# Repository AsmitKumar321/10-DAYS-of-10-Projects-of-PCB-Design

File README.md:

# 10-DAYS-of-10-Projects-of-PCB-Design
DAY 01: AC to DC converter

DAY 02: Transformerless Power Supply

DAY 03: SERVO MOTOR TESTER

DAY 04: DC MOTOR SPEED CONTROLLER

DAY 05: USB TO UART CONVERTER

DAY 06: DC-DC BOOST CONVERTER

DAY 07: MOTOR DRIVER

DAY 08: 30A HOME AUTOMATION WITH ESP32 MCUP

DAY 09: 300 WATT SINE WAVE INVERTER

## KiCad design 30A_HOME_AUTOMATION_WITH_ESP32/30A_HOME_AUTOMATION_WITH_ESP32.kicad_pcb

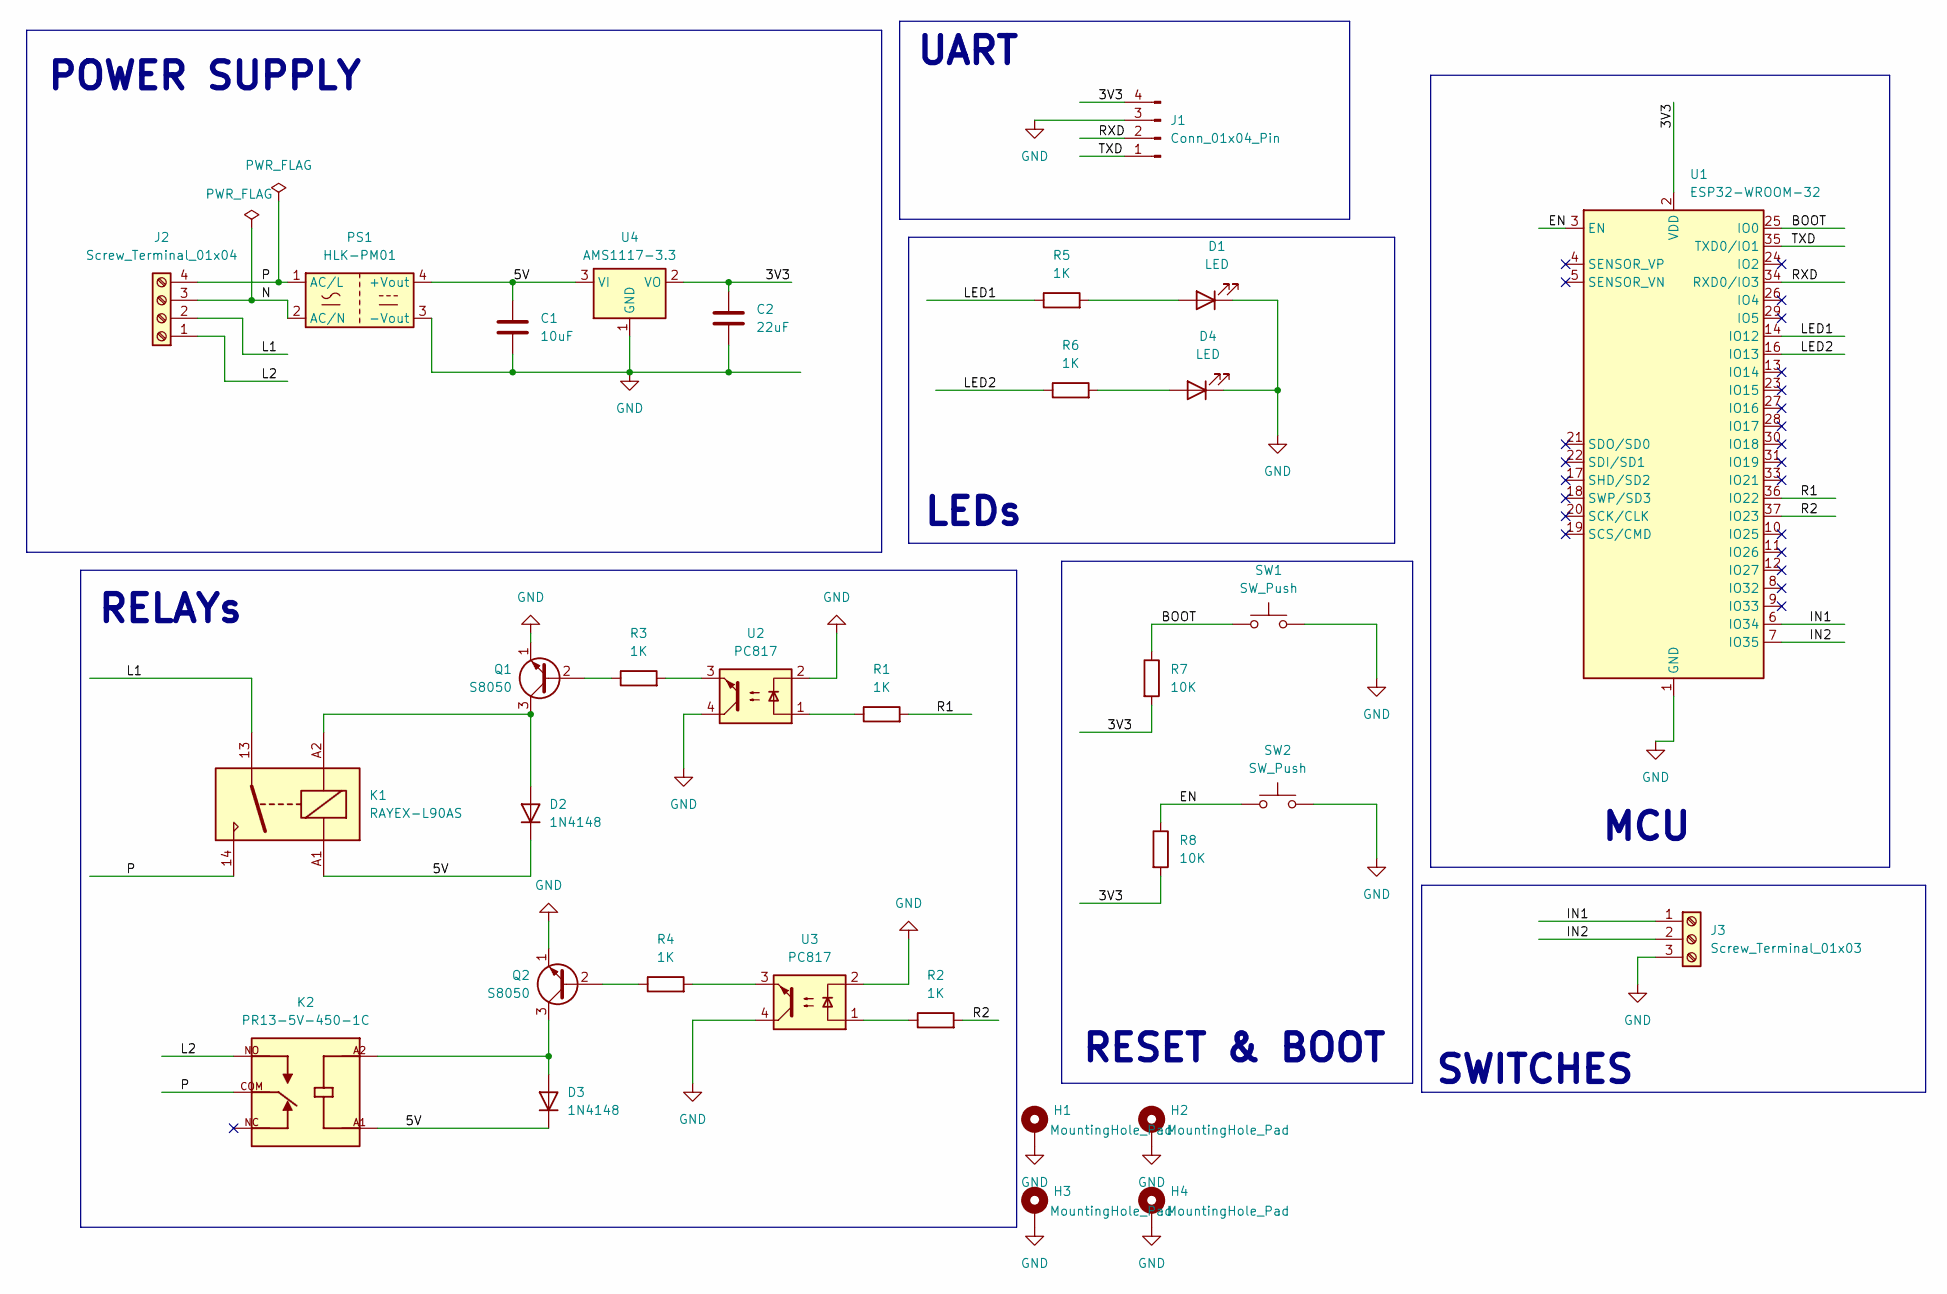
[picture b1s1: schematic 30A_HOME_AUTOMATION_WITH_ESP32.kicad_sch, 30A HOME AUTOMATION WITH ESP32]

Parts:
C1: 10uF; C_0805_2012Metric
C2: 22uF; C_0805_2012Metric
D1, D4: LED; LED_0805_2012Metric
D2, D3: 1N4148; D_DO-35_SOD27_P7.62mm_Horizontal
H1, H2, H3, H4: MountingHole_Pad; MountingHole_2.7mm_M2.5_Pad_Via
J1: Conn_01x04_Pin; PinHeader_1x04_P2.54mm_Vertical
J2: Screw_Terminal_01x04; TerminalBlock_bornier-4_P5.08mm
J3: Screw_Terminal_01x03; TerminalBlock_bornier-3_P5.08mm
K1: RAYEX-L90AS; Relay_SPST_RAYEX-L90AS
K2: PR13-5V-450-1C; RELAY_PR13-5V-450-1C; PARTREV 1.0
PS1: HLK-PM01; Converter_ACDC_Hi-Link_HLK-PMxx
Q1, Q2: S8050; TO-92_Inline
R1, R2, R3, R4, R5, R6: 1K; R_0805_2012Metric
R7, R8: 10K; R_0805_2012Metric
SW1, SW2: SW_Push; SW_PUSH_6mm
U1: ESP32-WROOM-32
U2, U3: PC817; DIP-4_W7.62mm
U4: AMS1117-3.3; SOT-223-3_TabPin2

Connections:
/3V3: C2.1, J1.4, R7.2, R8.2, U1.2 (VDD), U4.2 (VO)
/5V: C1.1, D2.1 (K), D3.1 (K), K1.A1, K2.A1, PS1.4 (+Vout), U4.3 (VI)
/BOOT: R7.1, SW1.1, U1.25 (IO0)
/EN: R8.1, SW2.1, U1.3 (EN)
/IN1: J3.1, U1.6 (IO34)
/IN2: J3.2, U1.7 (IO35)
/L1: J2.2, K1.13
/L2: J2.1, K2.NO
/LED1: R5.1, U1.14 (IO12)
/LED2: R6.1, U1.16 (IO13)
/N: J2.3, PS1.2 (AC/N)
/P: J2.4, K1.14, K2.COM, PS1.1 (AC/L)
/R1: R1.2, U1.36 (IO22)
/R2: R2.2, U1.37 (IO23)
/RXD: J1.2, U1.34 (RXD0/IO3)
/TXD: J1.1, U1.35 (TXD0/IO1)
GND: C1.2, C2.2, D1.1 (K), D4.1 (K), H1.1, H2.1, H3.1, H4.1, J1.3, J3.3, PS1.3 (-Vout), Q1.1 (E), Q2.1 (E), SW1.2, SW2.2, U1.1 (GND), U1.15 (GND), U1.38 (GND), U1.39 (GND), U2.2, U2.4, U3.2, U3.4, U4.1 (GND)
unnamed: D1.2 (A), R5.2
unnamed: D2.2 (A), K1.A2, Q1.3 (C)
unnamed: D3.2 (A), K2.A2, Q2.3 (C)
unnamed: D4.2 (A), R6.2
unnamed: Q1.2 (B), R3.1
unnamed: Q2.2 (B), R4.1
unnamed: R1.1, U2.1
unnamed: R2.1, U3.1
unnamed: R3.2, U2.3
unnamed: R4.2, U3.3

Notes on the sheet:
SWITCHES
LEDs
RELAYs
UART
RESET & BOOT
POWER SUPPLY
MCU

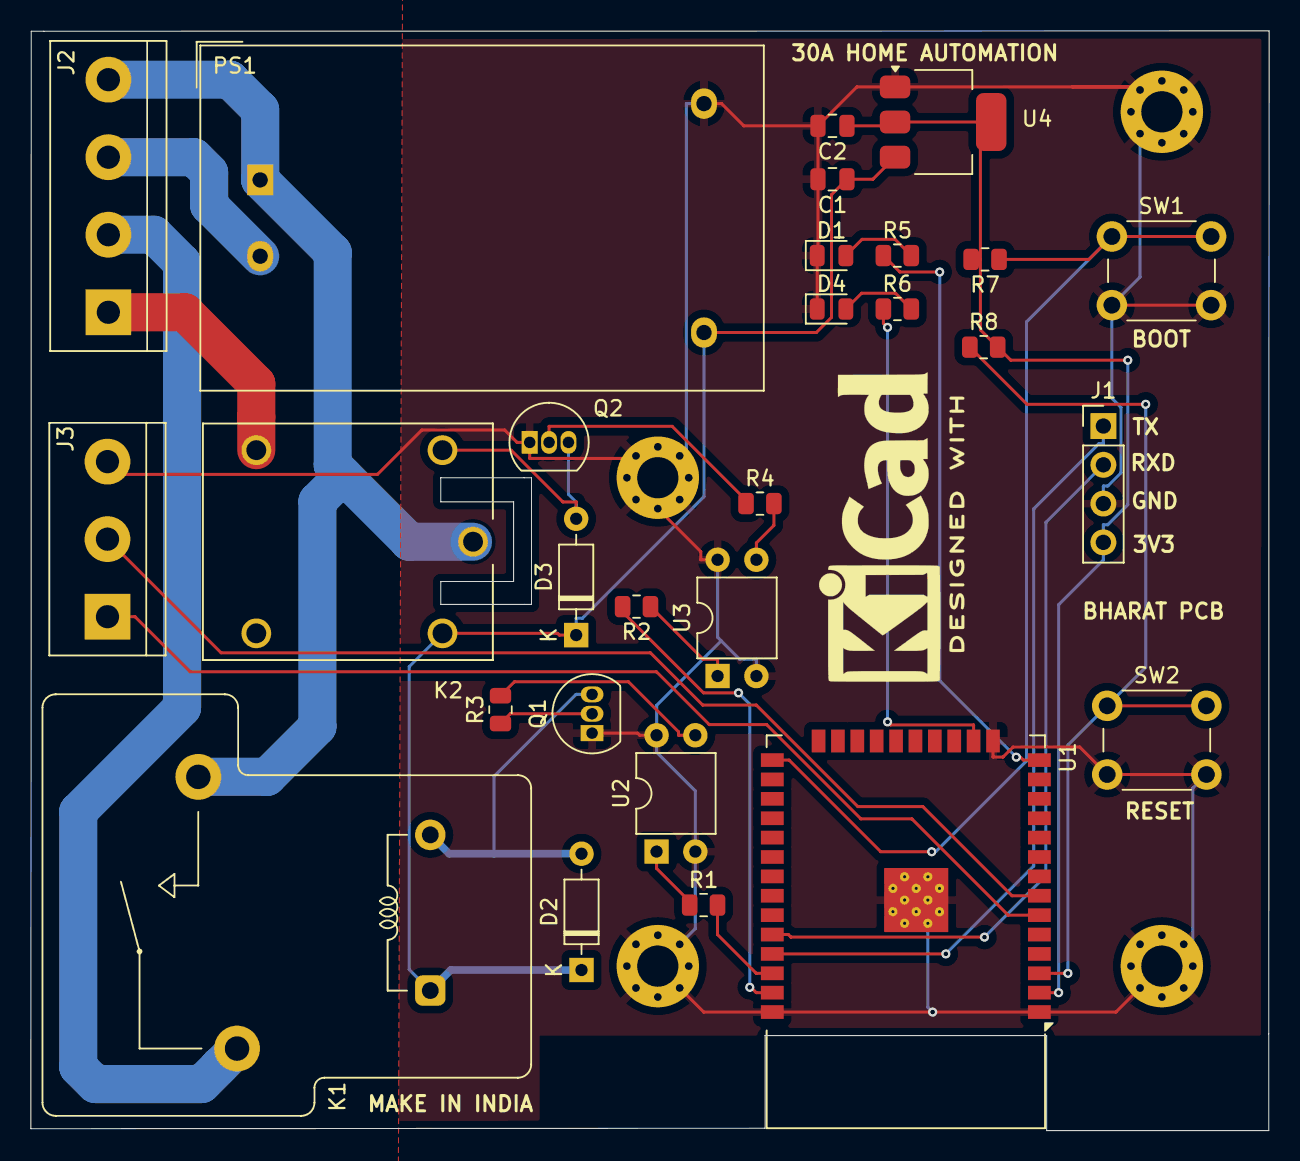
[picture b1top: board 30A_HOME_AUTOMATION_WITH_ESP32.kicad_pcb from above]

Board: 2 copper layers, 81.1 x 72.1 mm, 32 parts (0 on the bottom side), 27 nets.

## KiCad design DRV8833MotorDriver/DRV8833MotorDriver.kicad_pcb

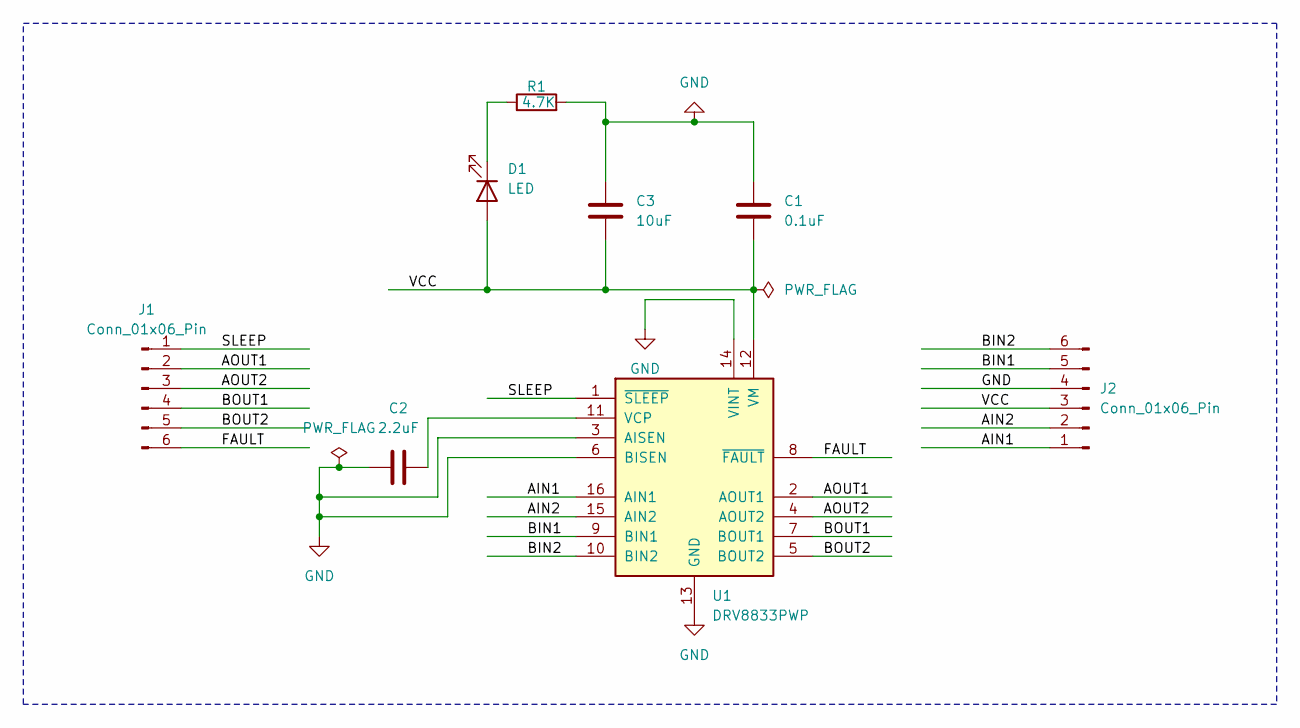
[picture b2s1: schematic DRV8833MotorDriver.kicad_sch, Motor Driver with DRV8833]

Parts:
C1: 0.1uF; C_0805_2012Metric
C2: 2.2uF; C_0805_2012Metric
C3: 10uF; CP_EIA-6032-20_AVX-F
D1: LED; LED_0805_2012Metric
J1, J2: Conn_01x06_Pin; PinHeader_1x06_P2.54mm_Vertical
R1: 4.7K; R_0805_2012Metric
U1: DRV8833PWP; HTSSOP-16-1EP_4.4x5mm_P0.65mm_EP3.4x5mm_Mask2.46x2.31mm_The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

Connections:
/AIN1: J2.1, U1.16 (AIN1)
/AIN2: J2.2, U1.15 (AIN2)
/AOUT1: J1.2, U1.2 (AOUT1)
/AOUT2: J1.3, U1.4 (AOUT2)
/BIN1: J2.5, U1.9 (BIN1)
/BIN2: J2.6, U1.10 (BIN2)
/BOUT1: J1.4, U1.7 (BOUT1)
/BOUT2: J1.5, U1.5 (BOUT2)
/FAULT: J1.6, U1.8 (~FAULT)
/SLEEP: J1.1, U1.1 (~SLEEP)
/VCC: C1.2, C3.2, D1.2 (A), J2.3, U1.12 (VM)
GND: C1.1, C2.1, C3.1, J2.4, R1.2, U1.3 (AISEN), U1.6 (BISEN), U1.13 (GND), U1.14 (VINT), U1.17 (GND)
unnamed: D1.1 (K), R1.1
unnamed: C2.2, U1.11 (VCP)

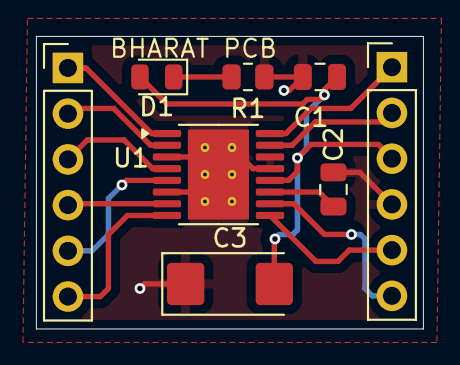
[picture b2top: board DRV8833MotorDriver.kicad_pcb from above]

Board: 2 copper layers, 21.5 x 16.2 mm, 8 parts (0 on the bottom side), 14 nets.

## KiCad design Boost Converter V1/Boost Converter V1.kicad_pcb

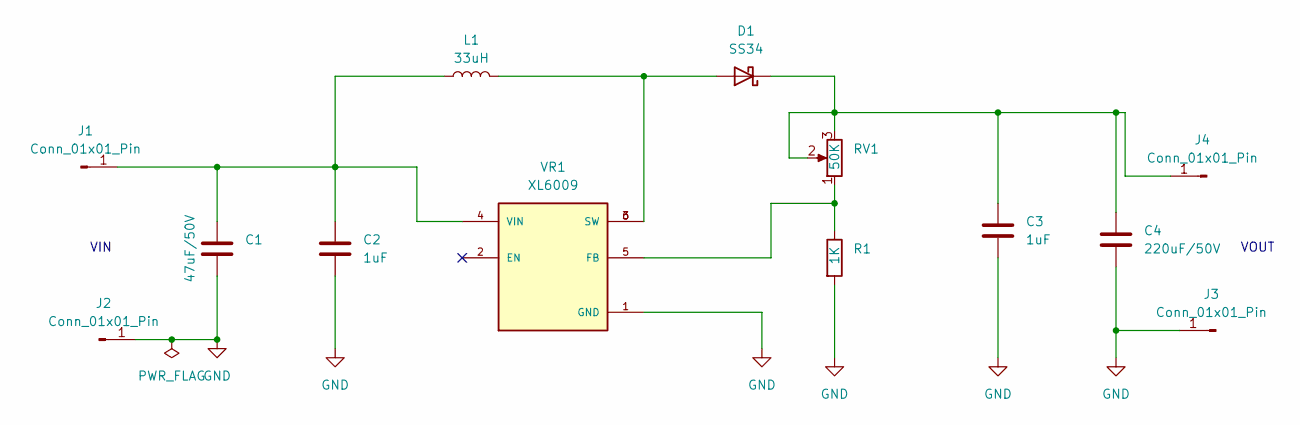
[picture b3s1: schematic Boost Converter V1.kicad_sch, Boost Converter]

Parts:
C1: 47uF/50V; C_Radial_D6.3mm_H11.0mm_P2.50mm
C2, C3: 1uF; C_0805_2012Metric
C4: 220uF/50V; C_Radial_D6.3mm_H11.0mm_P2.50mm
D1: SS34; D_SMA
J1, J2, J3, J4: Conn_01x01_Pin; PinHeader_1x01_P2.54mm_Vertical
L1: 33uH; L_12x12mm_H8mm
R1: 1K; R_1206_3216Metric
RV1: 50K; Potentiometer_Bourns_3296W_Vertical
VR1: XL6009; DPAK170P1435X465-6N; PARTREV 1.1

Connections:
GND: C1.2, C2.2, C3.2, C4.2, J2.1, J3.1, R1.2, VR1.1 (GND)
unnamed: D1.2 (A), L1.2, VR1.3 (SW), VR1.6 (SW)
unnamed: C3.1, C4.1, D1.1 (K), J4.1, RV1.2, RV1.3
unnamed: C1.1, C2.1, J1.1, L1.1, VR1.4 (VIN)
unnamed: R1.1, RV1.1, VR1.5 (FB)

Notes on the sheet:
VIN
VOUT

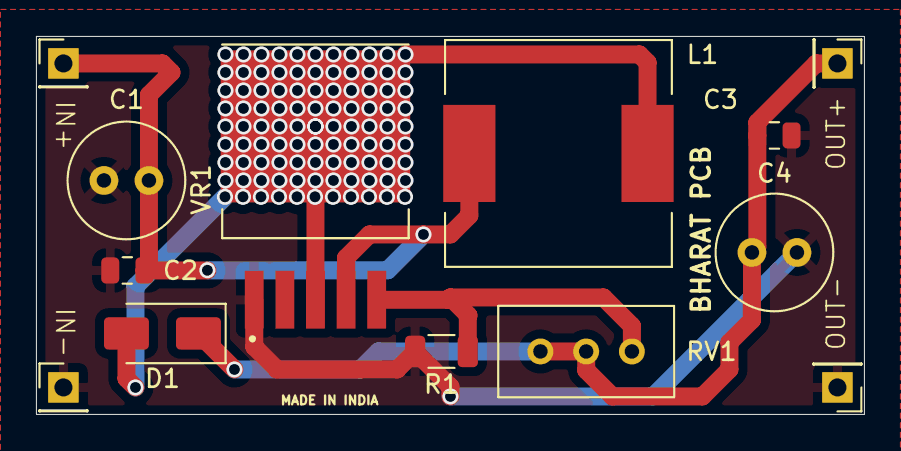
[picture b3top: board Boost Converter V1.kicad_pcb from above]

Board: 2 copper layers, 46.0 x 21.0 mm, 13 parts (0 on the bottom side), 5 nets.

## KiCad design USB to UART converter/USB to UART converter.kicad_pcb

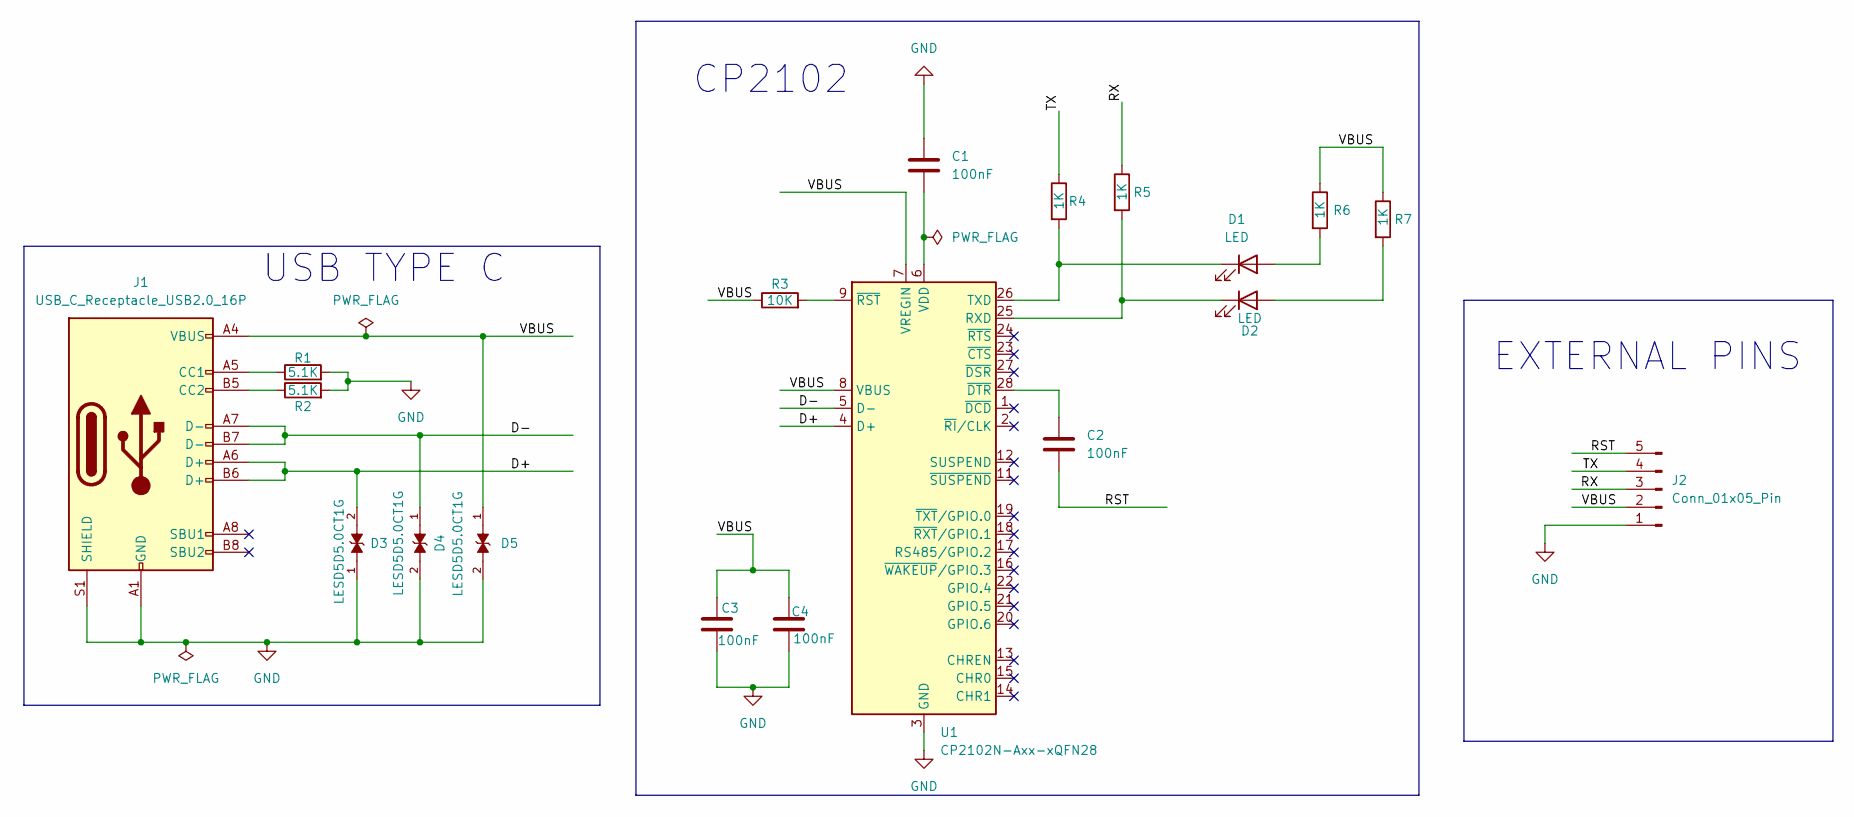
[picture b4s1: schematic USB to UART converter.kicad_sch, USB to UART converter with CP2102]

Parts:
C1, C2, C3, C4: 100nF; C_0201_0603Metric
D1, D2: LED; LED_0201_0603Metric
D3, D4, D5: LESD5D5.0CT1G; TVS_LESD5D5.0CT1G; PARTREV O
J1: USB_C_Receptacle_USB2.0_16P; USB_C_Receptacle_HRO_TYPE-C-31-M-12
J2: Conn_01x05_Pin; PinHeader_1x05_P2.54mm_Horizontal
R1, R2: 5.1K; R_0201_0603Metric
R3: 10K; R_0201_0603Metric
R4, R5, R6, R7: 1K; R_0201_0603Metric
U1: CP2102N-Axx-xQFN28; QFN-28-1EP_5x5mm_P0.5mm_EP3.35x3.35mm

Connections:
/D+: D3.2, J1.A6 (D+), J1.B6 (D+), U1.4 (D+)
/D-: D4.1, J1.A7 (D-), J1.B7 (D-), U1.5 (D-)
/RST: C2.2, J2.5
/RX: J2.3, R5.1
/TX: J2.4, R4.1
/VBUS: C3.1, C4.1, D5.1, J1.A4 (VBUS), J1.A9 (VBUS), J1.B4 (VBUS), J1.B9 (VBUS), J2.2, R3.1, R6.1, R7.1, U1.7 (VREGIN), U1.8 (VBUS)
GND: C1.1, C3.2, C4.2, D3.1, D4.2, D5.2, J1.A1 (GND), J1.A12 (GND), J1.B1 (GND), J1.B12 (GND), J1.S1 (SHIELD), J2.1, R1.2, R2.2, U1.3 (GND), U1.29 (GND)
unnamed: D1.2 (A), R6.2
unnamed: D1.1 (K), R4.2, U1.26 (TXD)
unnamed: D2.2 (A), R7.2
unnamed: D2.1 (K), R5.2, U1.25 (RXD)
unnamed: J1.A5 (CC1), R1.1
unnamed: J1.B5 (CC2), R2.1
unnamed: C1.2, U1.6 (VDD)
unnamed: C2.1, U1.28 (~DTR)
unnamed: R3.2, U1.9 (~RST)

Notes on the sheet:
CP2102
USB TYPE C
EXTERNAL PINS

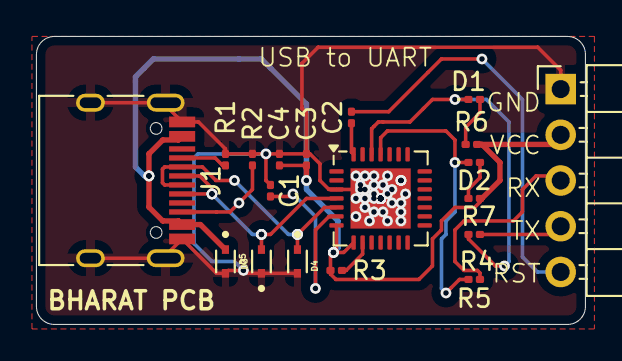
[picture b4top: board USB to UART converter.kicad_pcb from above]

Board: 2 copper layers, 30.5 x 16.0 mm, 19 parts (0 on the bottom side), 16 nets.

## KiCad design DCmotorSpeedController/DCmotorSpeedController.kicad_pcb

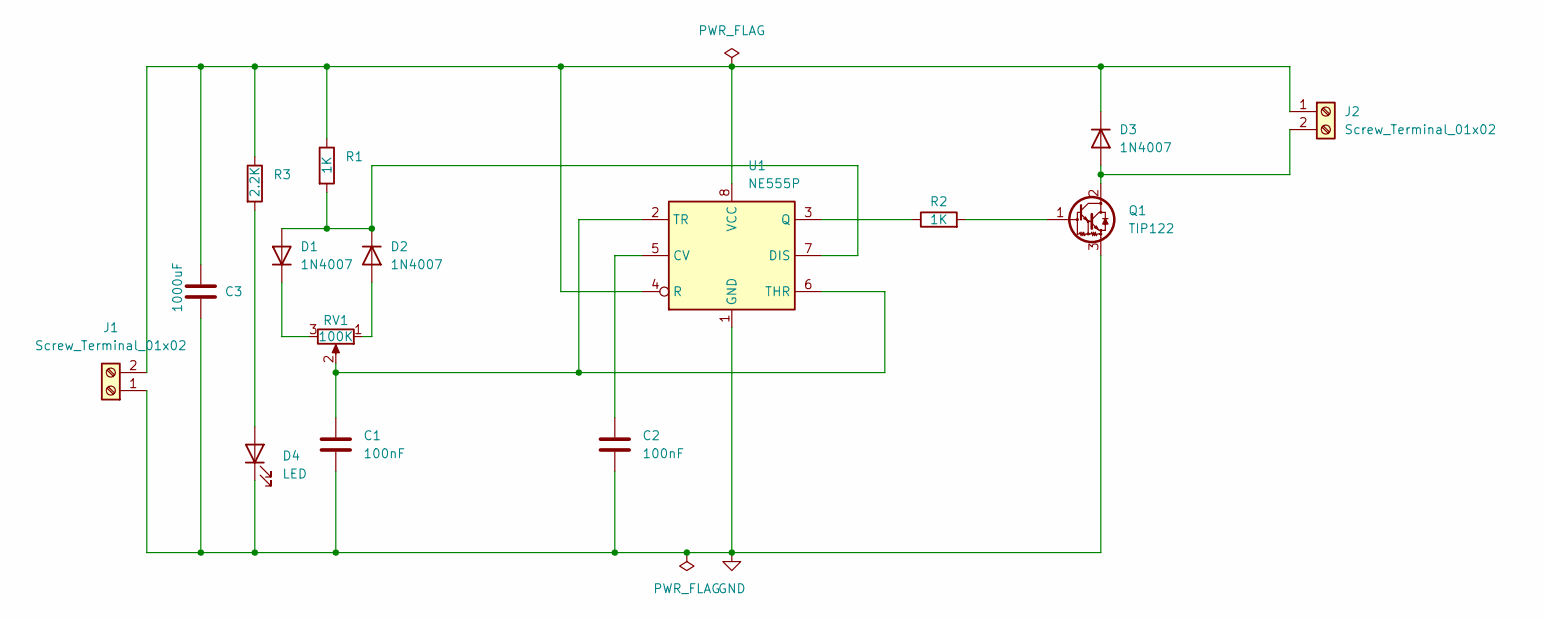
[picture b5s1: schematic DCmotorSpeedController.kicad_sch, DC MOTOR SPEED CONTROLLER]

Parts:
C1, C2: 100nF; C_Disc_D4.7mm_W2.5mm_P5.00mm
C3: 1000uF; CP_Radial_D10.0mm_P5.00mm
D1, D2, D3: 1N4007; D_DO-41_SOD81_P10.16mm_Horizontal
D4: LED; LED_D5.0mm
J1, J2: Screw_Terminal_01x02; TerminalBlock_bornier-2_P5.08mm
Q1: TIP122; TO-220-3_Vertical
R1, R2: 1K; R_Axial_DIN0204_L3.6mm_D1.6mm_P7.62mm_Horizontal
R3: 2.2K; R_Axial_DIN0204_L3.6mm_D1.6mm_P7.62mm_Horizontal
RV1: 100K; Potentiometer_Alps_RK163_Single_Horizontal
U1: NE555P; DIP-8_W7.62mm

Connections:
GND: C1.2, C2.2, C3.2, D4.1 (K), J1.1, Q1.3 (E), U1.1 (GND)
unnamed: D1.2 (A), D2.1 (K), R1.2, U1.7 (DIS)
unnamed: D1.1 (K), RV1.3
unnamed: D2.2 (A), RV1.1
unnamed: D3.2 (A), J2.2, Q1.2 (C)
unnamed: C3.1, D3.1 (K), J1.2, J2.1, R1.1, R3.1, U1.4 (R), U1.8 (VCC)
unnamed: D4.2 (A), R3.2
unnamed: Q1.1 (B), R2.2
unnamed: C2.1, U1.5 (CV)
unnamed: R2.1, U1.3 (Q)
unnamed: C1.1, RV1.2, U1.2 (TR), U1.6 (THR)

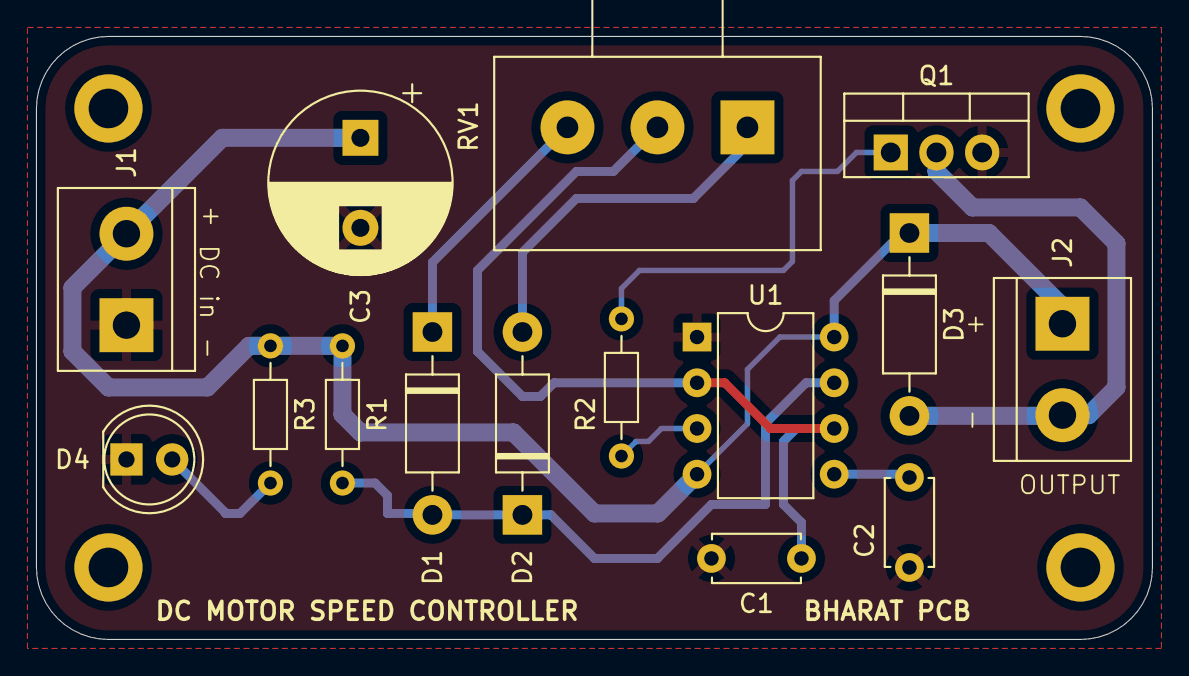
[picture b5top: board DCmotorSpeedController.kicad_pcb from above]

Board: 2 copper layers, 62.0 x 33.5 mm, 15 parts (0 on the bottom side), 11 nets.

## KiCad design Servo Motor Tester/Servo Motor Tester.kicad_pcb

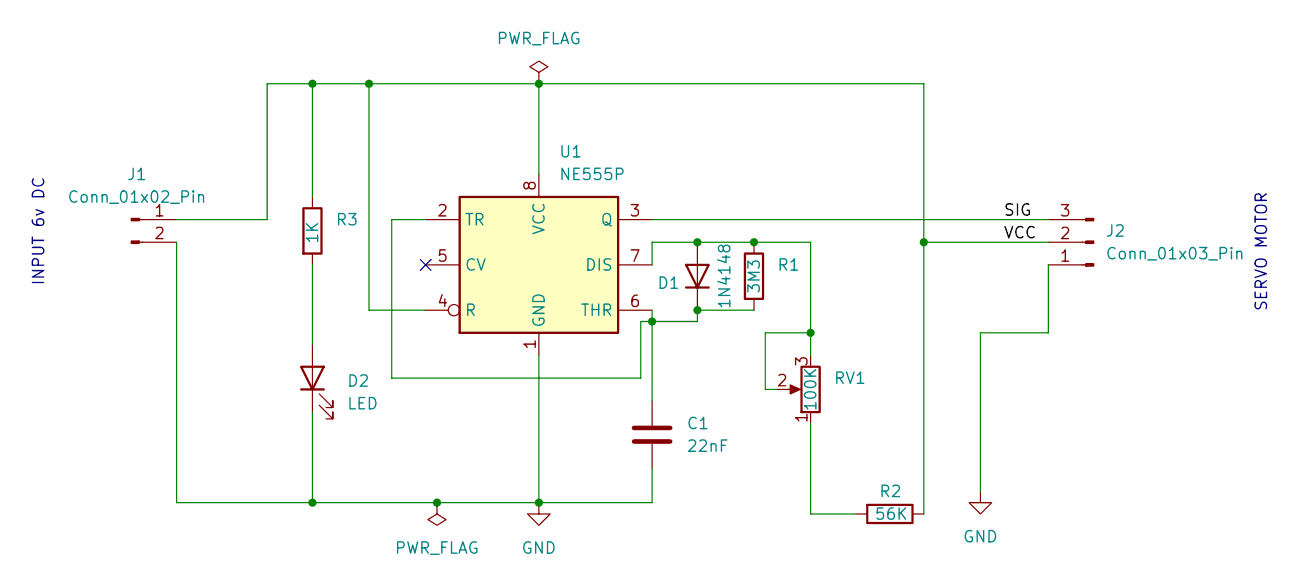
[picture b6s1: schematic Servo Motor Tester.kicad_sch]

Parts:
C1: 22nF; C_Disc_D4.3mm_W1.9mm_P5.00mm
D1: 1N4148; D_DO-35_SOD27_P7.62mm_Horizontal
D2: LED; LED_D3.0mm
J1: Conn_01x02_Pin; PinHeader_1x02_P2.54mm_Horizontal
J2: Conn_01x03_Pin; PinHeader_1x03_P2.54mm_Horizontal
R1: 3M3; R_Axial_DIN0204_L3.6mm_D1.6mm_P7.62mm_Horizontal
R2: 56K; R_Axial_DIN0204_L3.6mm_D1.6mm_P7.62mm_Horizontal
R3: 1K; R_Axial_DIN0204_L3.6mm_D1.6mm_P7.62mm_Horizontal
RV1: 100K; Potentiometer_Alps_RK163_Single_Horizontal
U1: NE555P; DIP-8_W7.62mm

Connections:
/SIG: J2.3, U1.3 (Q)
/VCC: J1.1, J2.2, R2.1, R3.1, U1.4 (R), U1.8 (VCC)
GND: C1.2, D2.1 (K), J1.2, J2.1, U1.1 (GND)
unnamed: D1.2 (A), R1.1, RV1.2, RV1.3, U1.7 (DIS)
unnamed: C1.1, D1.1 (K), R1.2, U1.2 (TR), U1.6 (THR)
unnamed: D2.2 (A), R3.2
unnamed: R2.2, RV1.1

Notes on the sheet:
INPUT 6v DC
SERVO MOTOR

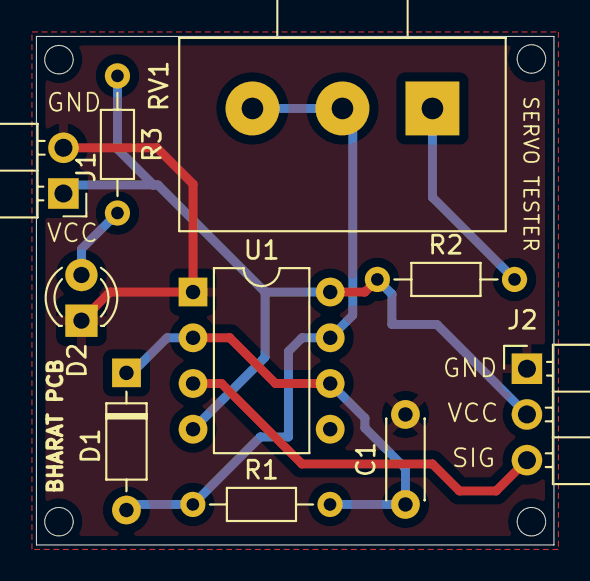
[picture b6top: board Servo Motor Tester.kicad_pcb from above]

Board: 2 copper layers, 28.8 x 28.2 mm, 10 parts (0 on the bottom side), 7 nets.

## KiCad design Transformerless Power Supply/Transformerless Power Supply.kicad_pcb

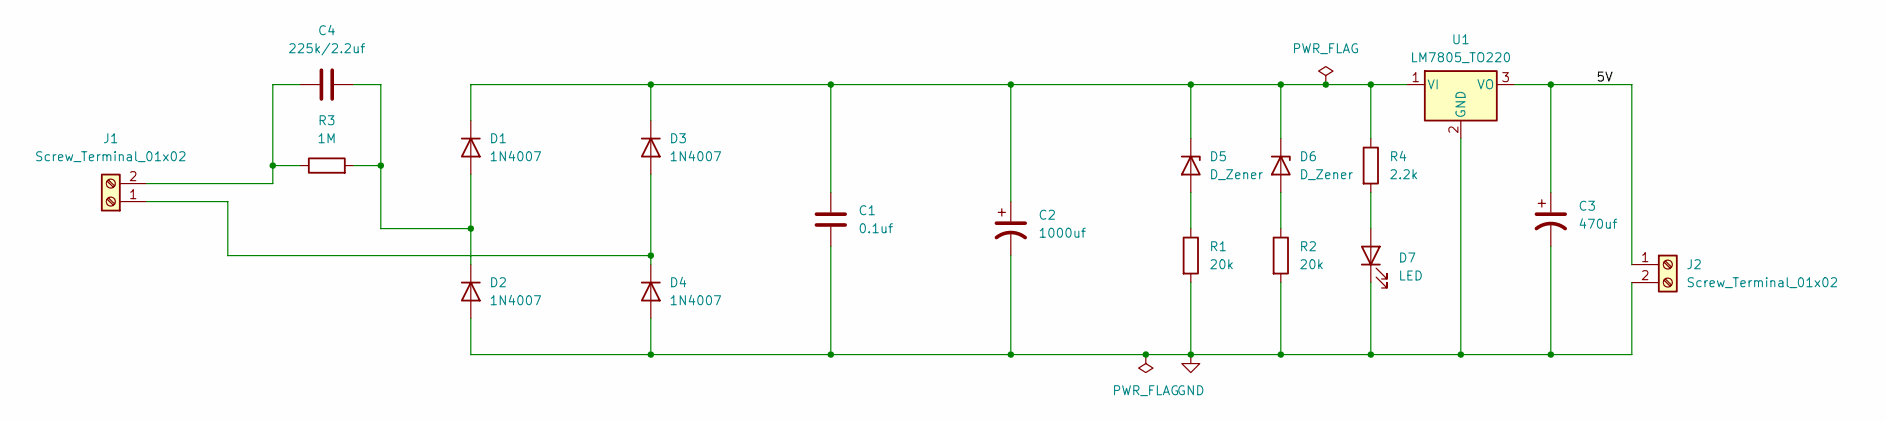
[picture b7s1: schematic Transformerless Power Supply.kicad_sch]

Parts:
C1: 0.1uf; C_Disc_D4.7mm_W2.5mm_P5.00mm
C2: 1000uf; CP_Radial_D10.0mm_P5.00mm
C3: 470uf; CP_Radial_D10.0mm_P3.80mm
C4: 225k/2.2uf; C_Rect_L18.0mm_W6.0mm_P15.00mm_FKS3_FKP3
D1, D2, D3, D4: 1N4007; D_DO-41_SOD81_P10.16mm_Horizontal
D5, D6: D_Zener; D_A-405_P7.62mm_Horizontal
D7: LED; LED_D5.0mm
J1, J2: Screw_Terminal_01x02; TerminalBlock_bornier-2_P5.08mm
R1, R2: 20k; R_Axial_DIN0207_L6.3mm_D2.5mm_P7.62mm_Horizontal
R3: 1M; R_Axial_DIN0207_L6.3mm_D2.5mm_P7.62mm_Horizontal
R4: 2.2k; R_Axial_DIN0207_L6.3mm_D2.5mm_P7.62mm_Horizontal
U1: LM7805_TO220; TO-220-3_Vertical

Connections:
/5V: C3.1, J2.1, U1.3 (VO)
GND: C1.2, C2.2, C3.2, D2.2 (A), D4.2 (A), D7.1 (K), J2.2, R1.2, R2.2, U1.2 (GND)
unnamed: C4.2, D1.2 (A), D2.1 (K), R3.2
unnamed: C1.1, C2.1, D1.1 (K), D3.1 (K), D5.1 (K), D6.1 (K), R4.1, U1.1 (VI)
unnamed: D3.2 (A), D4.1 (K), J1.1
unnamed: D5.2 (A), R1.1
unnamed: D6.2 (A), R2.1
unnamed: D7.2 (A), R4.2
unnamed: C4.1, J1.2, R3.1

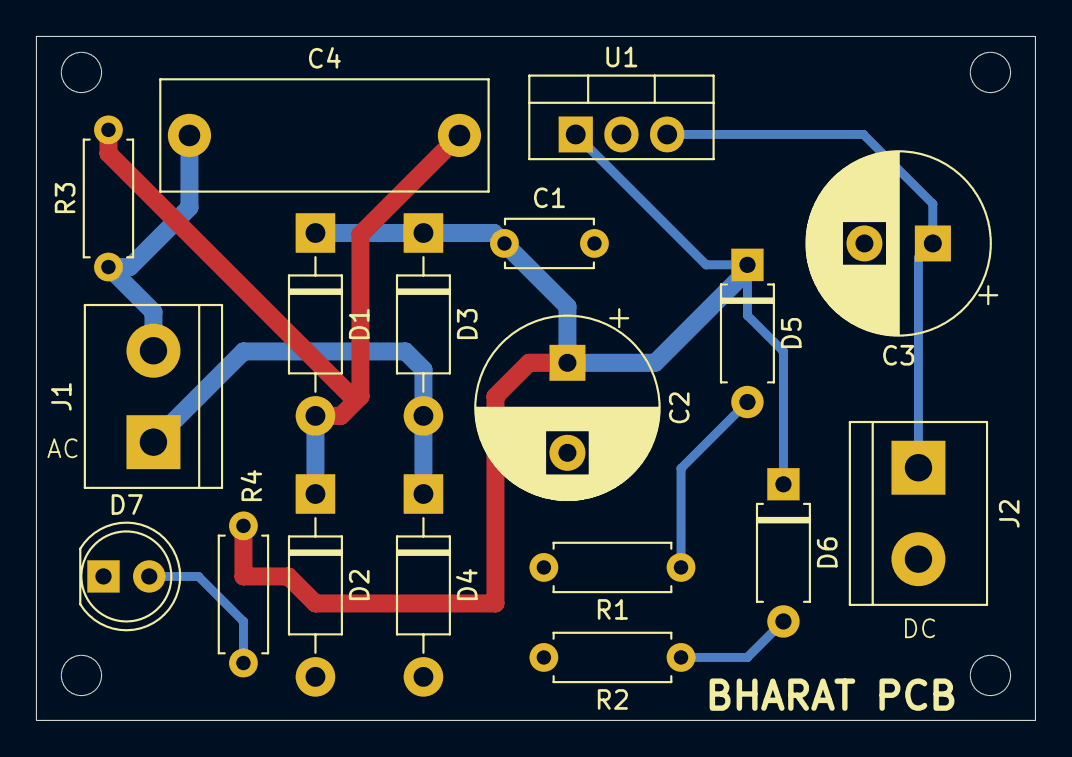
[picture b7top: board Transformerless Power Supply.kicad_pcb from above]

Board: 2 copper layers, 55.5 x 38.0 mm, 18 parts (0 on the bottom side), 9 nets.

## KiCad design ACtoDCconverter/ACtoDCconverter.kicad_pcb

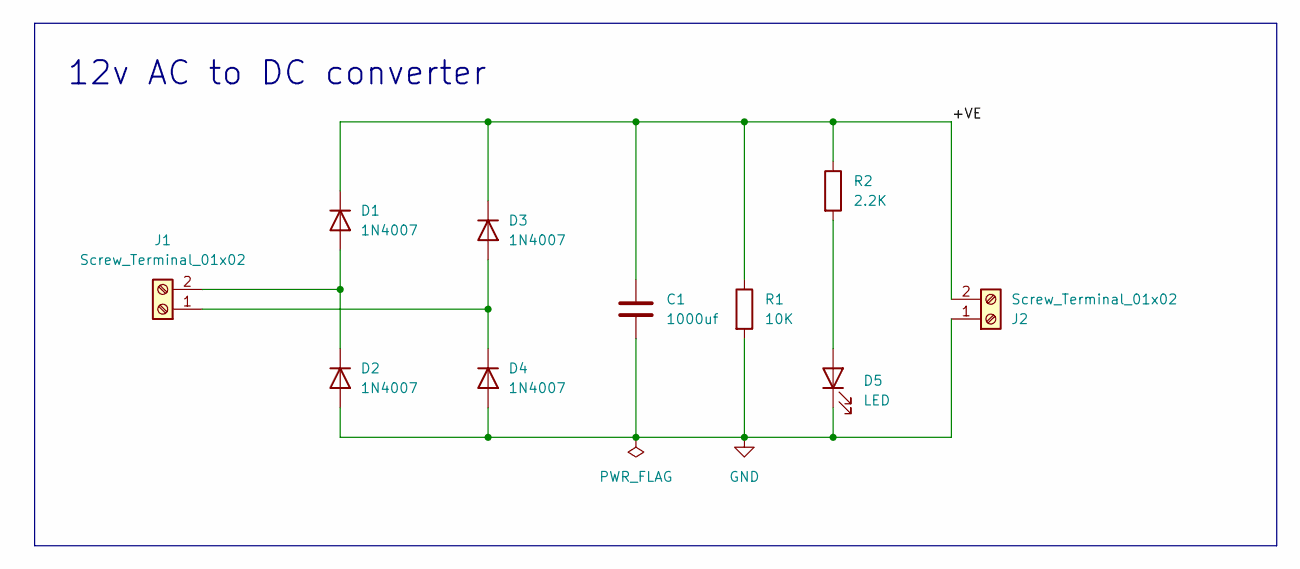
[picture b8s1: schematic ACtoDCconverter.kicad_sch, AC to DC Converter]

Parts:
C1: 1000uf; C_Radial_D8.0mm_H11.5mm_P3.50mm
D1, D2, D3, D4: 1N4007; D_DO-41_SOD81_P10.16mm_Horizontal
D5: LED; LED_D5.0mm
J1, J2: Screw_Terminal_01x02; TerminalBlock_bornier-2_P5.08mm
R1: 10K; R_Axial_DIN0207_L6.3mm_D2.5mm_P7.62mm_Horizontal
R2: 2.2K; R_Axial_DIN0207_L6.3mm_D2.5mm_P7.62mm_Horizontal

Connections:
/+VE: C1.1, D1.1 (K), D3.1 (K), J2.2, R1.1, R2.1
GND: C1.2, D2.2 (A), D4.2 (A), D5.1 (K), J2.1, R1.2
unnamed: D1.2 (A), D2.1 (K), J1.2
unnamed: D3.2 (A), D4.1 (K), J1.1
unnamed: D5.2 (A), R2.2

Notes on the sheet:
12v AC to DC converter

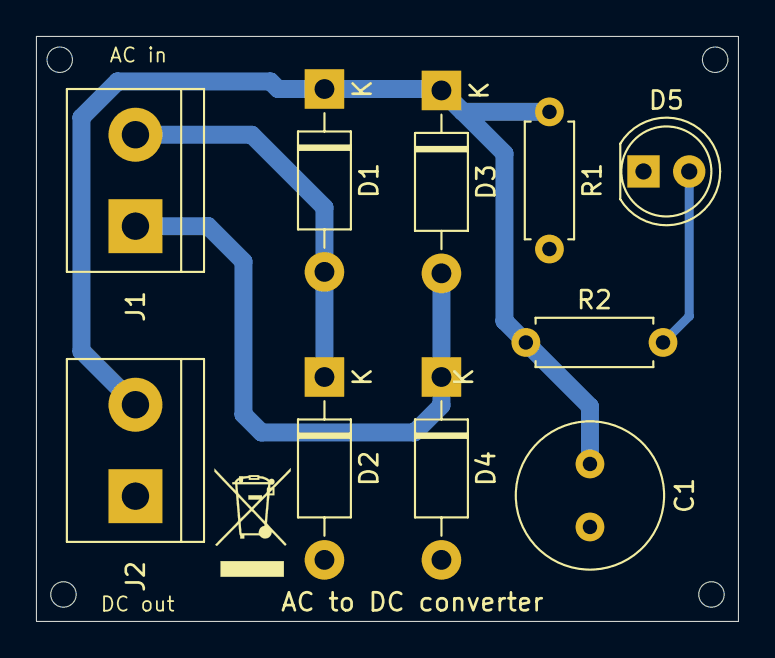
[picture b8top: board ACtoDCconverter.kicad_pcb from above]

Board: 2 copper layers, 39.0 x 32.5 mm, 10 parts (0 on the bottom side), 5 nets.
